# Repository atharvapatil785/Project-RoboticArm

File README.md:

# Project-RoboticArm :
Hello viewers this is my project on Robotic-Arm. 
<br>
Author - Atharva Patil (E&TC)

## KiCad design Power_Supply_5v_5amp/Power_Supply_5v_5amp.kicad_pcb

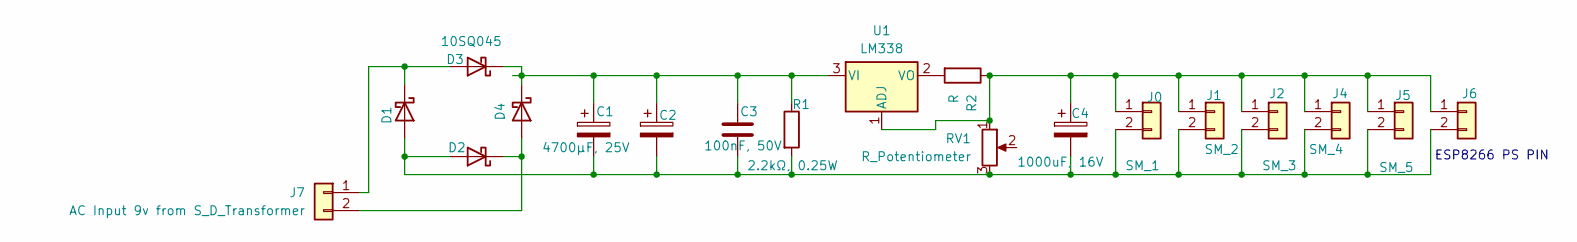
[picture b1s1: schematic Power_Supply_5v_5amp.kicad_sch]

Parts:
C1: 4700µF, 25V; CP_Radial_D18.0mm_P7.50mm
C2: CP_Radial_D18.0mm_P7.50mm
C3: 100nF, 50V; C_Disc_D5.0mm_W2.5mm_P5.00mm
C4: 1000uF, 16V; CP_Radial_D10.0mm_P5.00mm
D1, D2, D4: D_P600_R-6_P12.70mm_Horizontal
D3: 10SQ045; D_P600_R-6_P12.70mm_Horizontal
J0: SM_1; PhoenixContact_MC_1,5_2-G-5.08_1x02_P5.08mm_Horizontal
J1: SM_2; PhoenixContact_MCV_1,5_2-G-5.08_1x02_P5.08mm_Vertical
J2: SM_3; PhoenixContact_MCV_1,5_2-G-5.08_1x02_P5.08mm_Vertical
J4: SM_4; PhoenixContact_MCV_1,5_2-G-5.08_1x02_P5.08mm_Vertical
J5: SM_5; PhoenixContact_MCV_1,5_2-G-5.08_1x02_P5.08mm_Vertical
J6: SM_6; PhoenixContact_MCV_1,5_2-G-5.08_1x02_P5.08mm_Vertical
J7: AC Input 9v from S_D_Transformer; PhoenixContact_MCV_1,5_2-G-5.08_1x02_P5.08mm_Vertical
R1: 2.2kΩ, 0.25W; R_Axial_DIN0207_L6.3mm_D2.5mm_P10.16mm_Horizontal
R2: R; R_Axial_DIN0207_L6.3mm_D2.5mm_P10.16mm_Horizontal
RV1: R_Potentiometer; Potentiometer_Bourns_3296W_Vertical
U1: LM338; TO-220-3_Vertical

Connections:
unnamed: C1.2, C2.2, C3.2, C4.2, D1.2 (A), D2.2 (A), J0.2, J1.2, J2.2, J4.2, J5.2, J6.2, R1.2, RV1.3
unnamed: D1.1 (K), D3.2 (A), J7.1
unnamed: D2.1 (K), D4.2 (A), J7.2
unnamed: C1.1, C2.1, C3.1, D3.1 (K), D4.1 (K), R1.1, U1.3 (VI)
unnamed: C4.1, J0.1, J1.1, J2.1, J4.1, J5.1, J6.1, R2.1, RV1.1, U1.1 (ADJ)
unnamed: R2.2, U1.2 (VO)

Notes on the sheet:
ESP8266 PS PIN

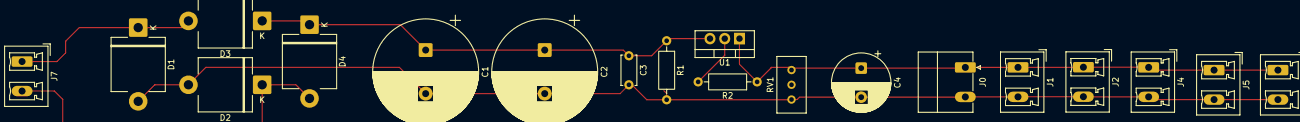
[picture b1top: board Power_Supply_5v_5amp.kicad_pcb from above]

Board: 2 copper layers, 19 parts (0 on the bottom side), 6 nets.

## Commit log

2026-01-05 Created file code.ino and edited readme
2026-01-07 added power supply schematics and other doc
